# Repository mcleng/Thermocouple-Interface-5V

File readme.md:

Thermocouple Interface | 5V
===========================

This work is licensed under a <a rel="license" href="http://creativecommons.org/licenses/by-sa/3.0/">Creative Commons Attribution-ShareAlike 3.0 Unported License</a>.

Designed By:

*	Ryan McLaughlin <ryan@ryanjmclaughlin.com>

Summary
-------

The single thermocouple interface was made out of the need to interface a micro controller to a thermocouple. One of the popular chips to perform a thermocouple to digital conversion is the MAX6675 (now MAX31855). While this is a great little chip it is a small surface mount part and therefore difficult to solder. The thermocouple interface board not only helps with having the chip broken out to a simple 0.1" header, but also provides a mini-thermocouple connector to easily interface to a thermocouple. Thermocouples are not designed to be soldered and this provides a good solid connection, while also using the proper metals in the connector required for a thermocouple connection.

This version of the board is a 5V compatible version of the interface. It is equipped with a MAX31855, along with the necessary voltage regulation and level shifting to allow for it to be directly hooked up to a 5V micro controller similar to an Arduino. The board comes fully assembled and includes a male and female header. Licensed under OSHW

Tutorial
--------

It is simple to get everything up and running.

1.	Install a header or solder jumper wires to the pin connections
2.	Connect a K-Type [Thermocouple](http://en.wikipedia.org/wiki/Thermocouple Thermocouple) to the PCB Thermocouple Connector use a Thermocouple Wire Connector if necessary
3.	Wire the necessary connections to an Arduino or other micro controller, the bare minimum connections are +V, GND, SCK, SO, CS
4.	If using an Arduino, load one of the samples from the MAX6675 Arduino Library and you should see temperature information in the serial console. With other micro controllers you can access the chip using a standard SPI interface. See MAX31855 data sheet for more details.

Board Specs
-----------

*	Dimensions: 1.25" x 1.50"
*	Chip: MAX31855, TXB0104
*	Voltage: 5V
*	Header: 1x6 0.1" Pitch
*	Fixturing: Four Corner Holes (1.20"x0.95" Spacing)

Versions
--------

###v2.0

Initial release of a 5V board with on-board level shifter. Other changes included:

* Initial release under Eagle 6.1 on Github
* PCB Production dates: 09-2011

Purchase
--------

[store.ryanjmclaughlin.com](http://store.ryanjmclaughlin.com). 

TODO
----

*	Do not route LED through level shifter

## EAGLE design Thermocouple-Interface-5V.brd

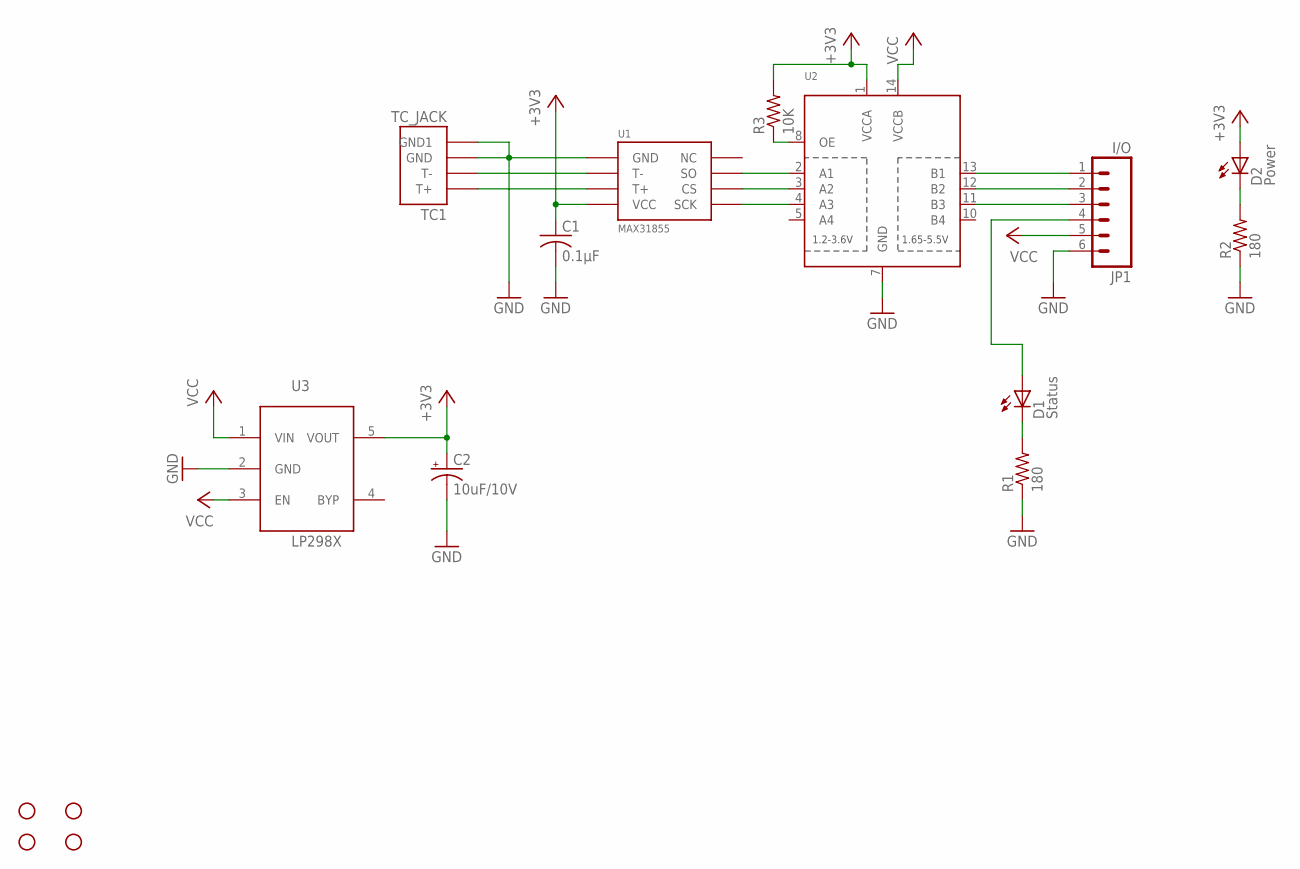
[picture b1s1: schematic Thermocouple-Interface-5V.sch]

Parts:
C1: 0.1µF; C0603
C2: 10uF/10V; A/3216-18R
D1: Status; CHIP-LED0805
D2: Power; CHIP-LED0805
JP1: I/O; 1X06
R1, R2: 180; R0603
R3: 10K; R0603
TC1: TC_JACK
U1: MAX31855; SOIC-8
U2: TXB0104PWR; TSSOP14
U3: LP298XS; SOT23-5L
U$1, U$2, U$3, U$4: STAND-OFF

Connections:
+3V3: C1.1, C2.+, D2.A, R3.2, U1.VCC, U2.1 (VCCA), U3.5 (VOUT)
CS: U1.CS, U2.3 (A2)
GND: C1.2, C2.-, JP1.6, R1.1, R2.1, TC1.P$1 (GND), TC1.P$2 (GND1), U1.GND, U2.7 (GND), U3.2 (GND)
unnamed: D1.C, R1.2
unnamed: D2.C, R2.2
unnamed: R3.1, U2.8 (OE)
unnamed: D1.A, JP1.4
SCK: U1.SCK, U2.4 (A3)
SO: U1.SO, U2.2 (A1)
T+: TC1.T+, U1.T+
T-: TC1.T-, U1.T-
VCC: JP1.5, U2.14 (VCCB), U3.1 (VIN), U3.3 (EN)
_CS: JP1.2, U2.12 (B2)
_SCK: JP1.3, U2.11 (B3)
_SO: JP1.1, U2.13 (B1)

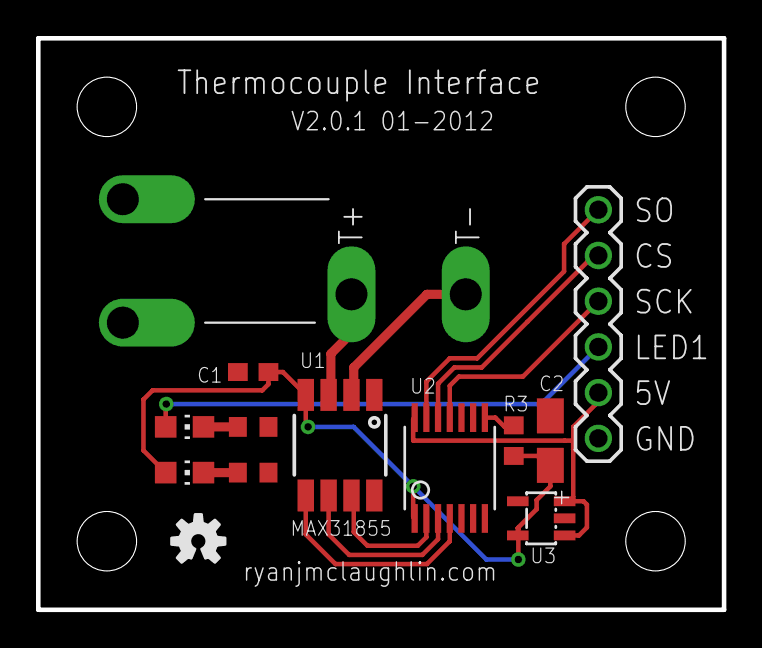
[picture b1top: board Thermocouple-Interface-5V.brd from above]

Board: 2 copper layers, 38.1 x 31.8 mm, 17 parts (0 on the bottom side), 15 nets.

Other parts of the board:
U$5: OSHW-LOGO-S

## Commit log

2012-01-29 Initial release to github, v2.0
2012-01-29 Status led no longer routes through level shifter, bumped to v2.0.1 for 01-2012 pcb production
2012-01-31 Added schematic and board images/pdf

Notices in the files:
readme.md:
CC BY-SA 3.0
